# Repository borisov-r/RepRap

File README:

This project is based on RepRap Mendel.

This repository will be the main source for the mechanics of our own version of RepRap with very precise X and Y movements.

===============================================

Mechanics:
Sketchup
CamBam / gcodes

===============================================

Firmware: is based on Tonokip

===============================================

Electronics: should be based on upcomming rfAtmega128 our design.

We should build prusa i3:
http://78.47.92.212/i3_documentation_pics/

===============================================

Main contributors to this project are:
Alexander
Radoslav
Pipo
Ruslan

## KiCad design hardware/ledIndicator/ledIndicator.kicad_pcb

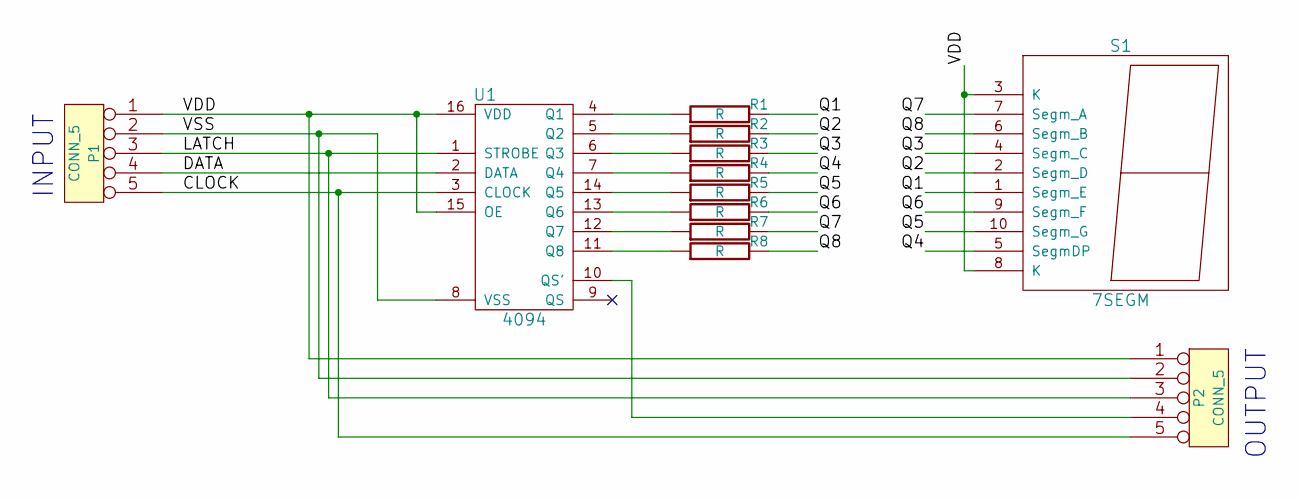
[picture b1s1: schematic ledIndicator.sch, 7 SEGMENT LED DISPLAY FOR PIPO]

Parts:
P1, P2: CONN_5; SMD_CONN5
R1, R2, R3, R4, R5, R6, R7, R8: R; SM0603_Resistor
S1: 7SEGM; SA56
U1: 4094; SO16N

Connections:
/CLOCK: P1.5, P2.5, U1.3 (CLOCK)
/DATA: P1.4, U1.2 (DATA)
/LATCH: P1.3, P2.3, U1.1 (STROBE)
/Q1: R1.2, S1.1 (Segm_E)
/Q2: R2.2, S1.2 (Segm_D)
/Q3: R3.2, S1.4 (Segm_C)
/Q4: R4.2, S1.5 (SegmDP)
/Q5: R5.2, S1.10 (Segm_G)
/Q6: R6.2, S1.9 (Segm_F)
/Q7: R7.2, S1.7 (Segm_A)
/Q8: R8.2, S1.6 (Segm_B)
/VDD: P1.1, P2.1, S1.3 (K), S1.8 (K), U1.15 (OE), U1.16 (VDD)
/VSS: P1.2, P2.2, U1.8 (VSS)
unnamed: P2.4, U1.10 (QS')
unnamed: R5.1, U1.14 (Q5)
unnamed: R6.1, U1.13 (Q6)
unnamed: R7.1, U1.12 (Q7)
unnamed: R8.1, U1.11 (Q8)
unnamed: R4.1, U1.7 (Q4)
unnamed: R3.1, U1.6 (Q3)
unnamed: R2.1, U1.5 (Q2)
unnamed: R1.1, U1.4 (Q1)

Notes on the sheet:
INPUT
OUTPUT

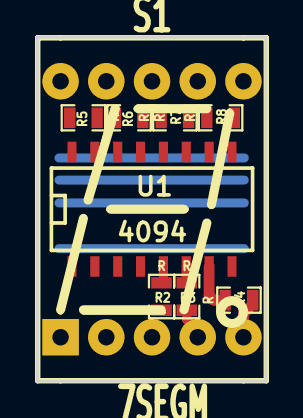
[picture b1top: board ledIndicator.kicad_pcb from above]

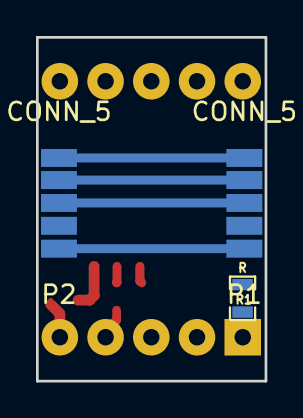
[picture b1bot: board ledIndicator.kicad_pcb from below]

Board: 2 copper layers, 12.7 x 19.1 mm, 12 parts (3 on the bottom side), 22 nets.

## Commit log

2012-05-25 added README
2012-05-25 Updated README file to more meaningfull thing.
2012-05-25 added main folder srtucture and README files to the directories
2012-05-25 Update mechanics/Sketchup/README
2012-05-25 Update mechanics/CamBam/README
2012-05-25 Update mechanics/CamBam/gcodes/README
2012-06-18 Added heatbed to hardware section. Size 17 x 15 cm for manufacturing.
2012-06-18 Image of calculated data.
2012-06-19 Timer 555 oscillator with NMOS high power transistor board.
2012-06-20 Added k-thermocouple initial design to hardware.
2012-06-22 New chopper opamp from farnell for the design.
2012-06-27 Added sketch of the pcb to the design.
2012-06-28 Added initial schematic.
2012-06-29 Schematic with AD8551 done and initial board started.
2012-07-02 Added resistor box .svg and BOM for K-thermocouple.
2012-07-06 Board started and pwr routed.
2012-07-15 Added smdComponentsBox to mechanics
2012-07-16 Simple thermistor single sided board done. Added BOM of the board.
2012-08-13 Added openscad file for pulleys generation and 27 tooth pulley DXF and STL files.
2012-08-15 Added some pulleys to mechanics.
2013-01-02 7 segment indicator added to hardware.
2013-01-03 Initial design of the layout on pcb
2013-01-15 Added ledIndicator.brd for previous KiCad version.
2013-01-23 Added ledIndicator gerber files for Pipo.
2013-01-31 Added settings for Sasho's Mendel 3D printer to support Sprinter firmware and to start printing 3D parts at last.
2013-01-31 Configuration for working Z axis.
2013-02-03 X, Y, Z calibrated and Extruder needs just a little more tunning.
2013-03-08 Added PrusaI3 blender files with mechanics and Sprinter firmware for RepRap Mendel at work.
2013-03-08 deleted firmware/README~
2013-03-28 Added PrusaI3 to repository with Bosch profiles.
2013-12-11 Latest changes to Sasho's Mendel. Z axis feed_homing fixed to 60 mm/s. Y axis is not inverted now and only thing that should be calibrated is extruder's feed rate.
2013-12-25 Last calibration of Sasho's extruder and XYZ axises
